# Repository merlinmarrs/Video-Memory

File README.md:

# Video-Memory

A series of PCBs to explore storing pixel information for VGA display.

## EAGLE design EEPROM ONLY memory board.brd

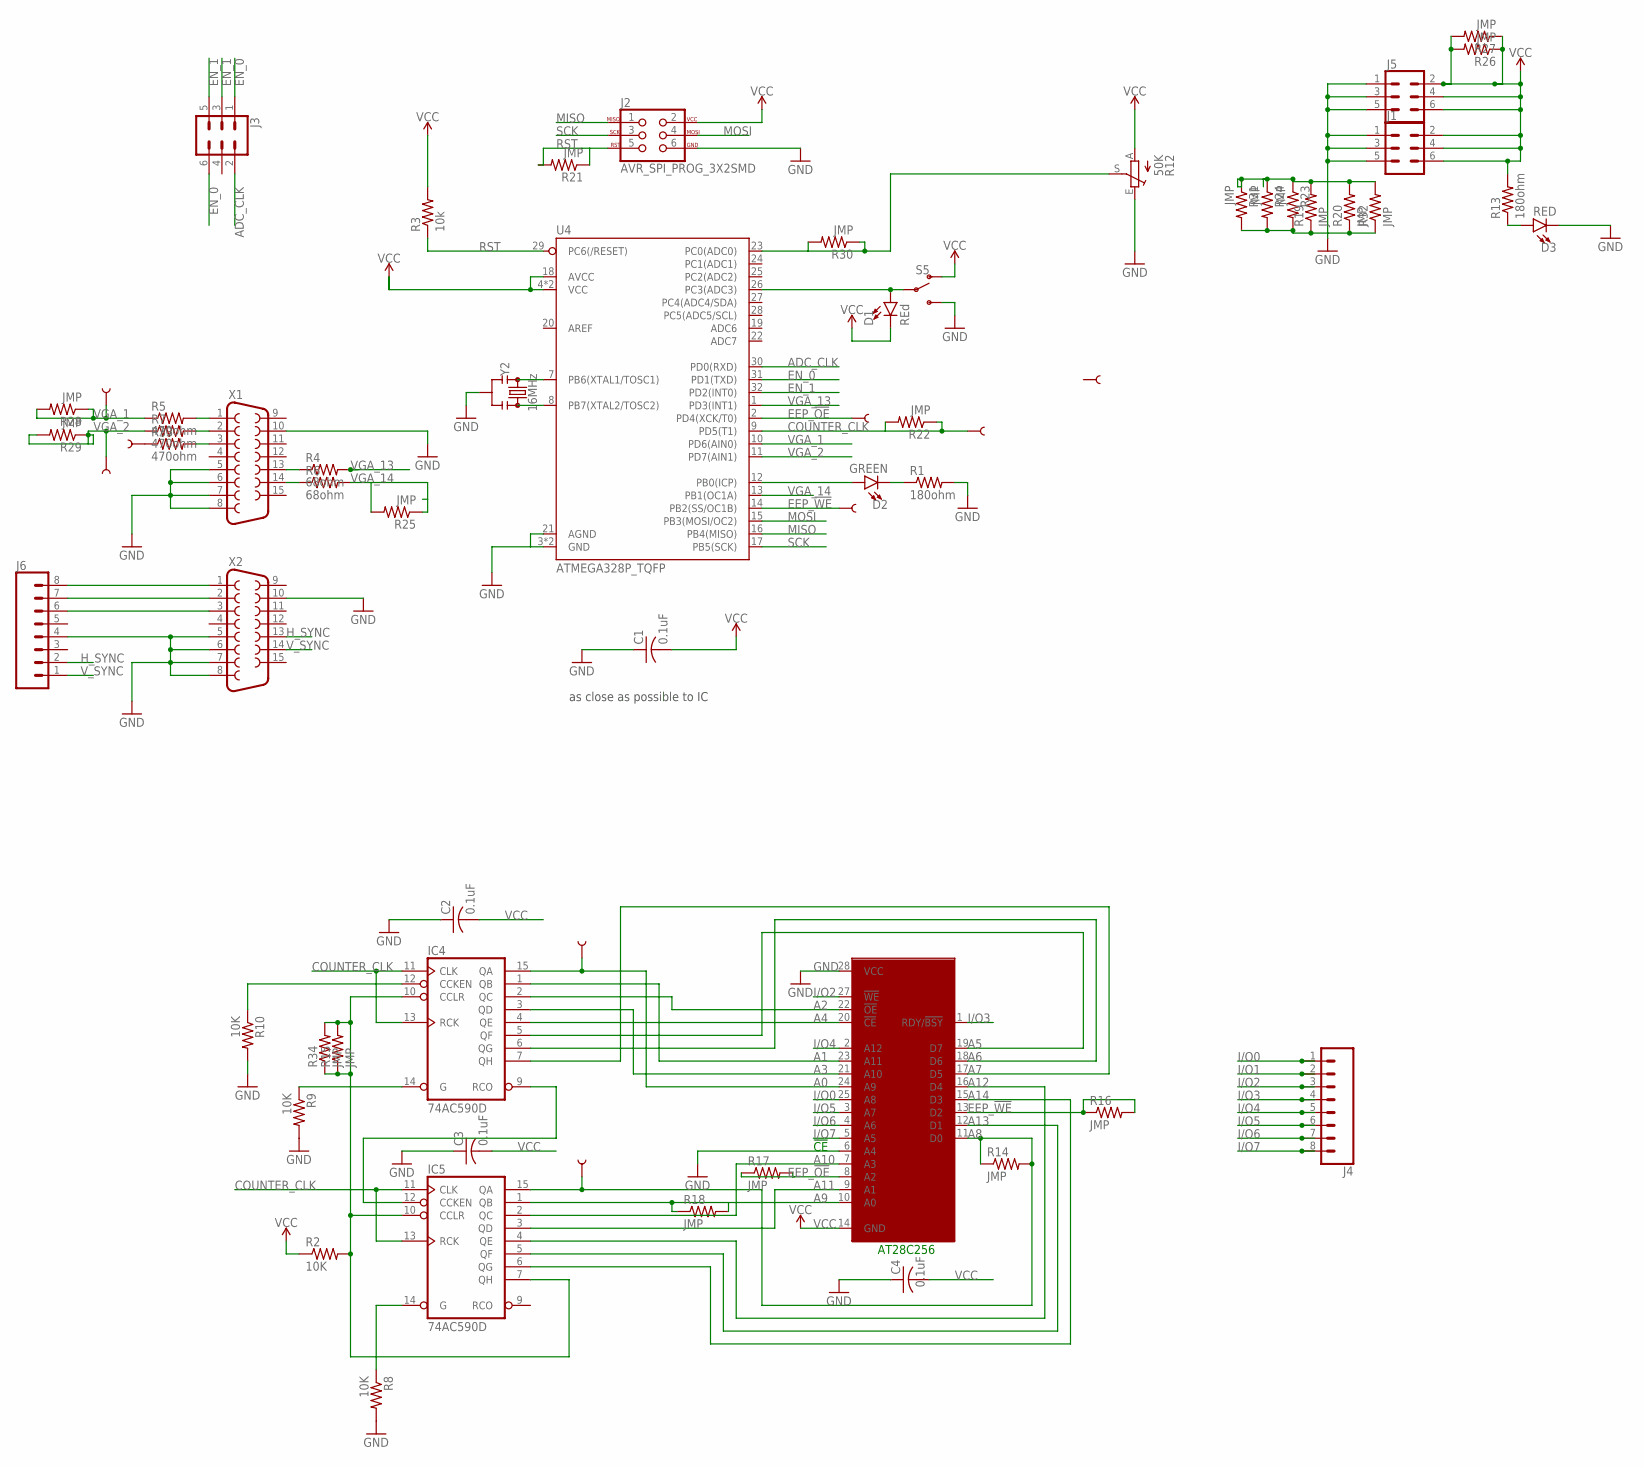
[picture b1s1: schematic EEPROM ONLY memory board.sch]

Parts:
C1, C2, C3, C4: 0.1uF; C1206
D1: REd; LED-1206
D2: GREEN; LED-1206
D3: RED; LED-1206
IC1: 28C64AVS; VSOP28-8X13
IC4, IC5: 74AC590D; SO16
J1, J3, J5: CONN_03X2FEMALE_SMD; 2X3_SMD
J2: AVR_SPI_PROG_3X2SMD; 2X3_SMT_POSTS
J4, J6: CONN_08SMD-STRAIGHT-ALT-FEMALE; 1X08_SMD_ALT
R1, R13: 180ohm; R1206
R2, R8, R9, R10: 10K; R1206
R3: 10k; R1206
R4, R6: 68ohm; R1206
R5, R7, R33: 470ohm; R1206
R12: 50K; CA9V
R14, R15, R16, R17, R18, R19, R20, R21, R22, R23, R24, R25, R26, R27, R28, R29, R30, R31, R32, R34: JMP; R1206
RX1, RX2, RX3, RX4, RX5, RX6, RX7, RX8, RX9: TEST-POINT3; PAD.03X.03
S5: SWITCH-SPDT-SMD-AYZ0202; SWITCH_DPDT_SMD_AYZ0202
U4: ATMEGA328P_TQFP; TQFP32-08
X1, X2: F15HP
Y2: 16MHz; RESONATOR-SMD-3.2X1.3

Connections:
A0: IC1.24 (A9), IC4.15 (QA), RX5.P$1
A1: IC1.23 (A11), IC4.1 (QB)
A2: IC1.22 (!OE), IC4.2 (QC)
A3: IC1.21 (A10), IC4.3 (QD)
A4: IC1.20 (!CE), IC4.4 (QE)
A5: IC1.19 (D7), IC4.5 (QF)
A6: IC1.18 (D6), IC4.6 (QG)
A7: IC1.17 (D5), IC4.7 (QH)
A8: IC1.11 (D0), IC5.15 (QA), R14.1, R14.2, RX6.P$1
A9: IC1.10 (A0), IC5.1 (QB), R18.1, R18.2
A10: IC1.7 (A3), IC5.2 (QC)
A11: IC1.9 (A1), IC5.3 (QD)
A12: IC1.16 (D4), IC5.4 (QE)
A13: IC1.12 (D1), IC5.5 (QF)
A14: IC1.15 (D3), IC5.6 (QG)
ADC_CLK: J3.2, U4.30 (PD0(RXD))
COUNTER_CLK: IC4.11 (CLK), IC4.13 (RCK), IC5.11 (CLK), IC5.13 (RCK), R22.1, R22.2, RX3.P$1, U4.9 (PD5(T1))
EEP_!OE: IC1.8 (A2), R17.1, R17.2, RX2.P$1, U4.2 (PD4(XCK/T0))
EEP_!WE: IC1.13 (D2), R16.1, R16.2, RX4.P$1, U4.14 (PB2(SS/OC1B))
EN_0: J3.1, J3.6, U4.31 (PD1(TXD))
EN_1: J3.3, J3.5, U4.32 (PD2(INT0))
GND: C1.1, C2.1, C3.1, C4.1, D3.C, IC1.6 (A4), IC1.28 (VCC), IC4.8 (GND), IC5.8 (GND), J1.1, J1.3, J1.5, J2.6, J5.1, J5.3, J5.5, J6.4, R1.2, R8.2, R9.2, R10.2, R12.E, R19.1, R19.2, R20.1, R20.2, R23.1, R23.2, R24.1, R24.2, R31.1, R31.2, R32.1, R32.2, S5.3 (S), U4.3 (GND), U4.5 (GND), U4.21 (AGND), X1.5, X1.6, X1.7, X1.8, X1.10, X2.5, X2.6, X2.7, X2.8, X2.10, Y2.2
H_SYNC: J6.2, X2.13
I/O0: IC1.25 (A8), J4.1
I/O1: J4.2
I/O2: IC1.27 (!WE), J4.3
I/O3: IC1.1 (RDY/!BSY), J4.4
I/O4: IC1.2 (A12), J4.5
I/O5: IC1.3 (A7), J4.6
I/O6: IC1.4 (A6), J4.7
I/O7: IC1.5 (A5), J4.8
MISO: J2.1, U4.16 (PB4(MISO))
MOSI: J2.4, U4.15 (PB3(MOSI/OC2))
unnamed: R5.2, X1.1
unnamed: R7.2, X1.2
unnamed: D3.A, R13.1
unnamed: R4.1, X1.13
unnamed: R6.1, X1.14
unnamed: IC4.9 (RCO), IC5.12 (CCKEN)
unnamed: U4.7 (PB6(XTAL1/TOSC1)), Y2.1
unnamed: U4.8 (PB7(XTAL2/TOSC2)), Y2.3
unnamed: IC5.14 (G), R8.1
unnamed: IC4.14 (G), R9.1
unnamed: IC4.12 (CCKEN), R10.1
unnamed: IC4.10 (CCLR), IC5.7 (QH), IC5.10 (CCLR), R2.2, R15.1, R15.2, R34.1, R34.2
unnamed: D1.A, S5.2, U4.26 (PC3(ADC3))
unnamed: J6.8, X2.1
unnamed: J6.7, X2.2
unnamed: D2.A, U4.12 (PB0(ICP))
unnamed: R33.2, X1.3
unnamed: D2.C, R1.1
unnamed: R33.1, RX7.P$1
unnamed: J6.6, X2.3
unnamed: R12.S, R30.1, R30.2, U4.23 (PC0(ADC0))
RST: J2.5, R3.1, R21.1, R21.2, U4.29 (PC6(/RESET))
SCK: J2.3, U4.17 (PB5(SCK))
VCC: C1.2, C2.2, C3.2, C4.2, D1.C, IC1.14 (GND), IC4.16 (VCC), IC5.16 (VCC), J1.2, J1.4, J1.6, J2.2, J5.2, J5.4, J5.6, R2.1, R3.2, R12.A, R13.2, R26.1, R26.2, R27.1, R27.2, S5.1 (O), U4.4 (VCC), U4.6 (VCC), U4.18 (AVCC)
VGA_1: R5.1, R28.1, R28.2, RX8.P$1, U4.10 (PD6(AIN0))
VGA_2: R7.1, R29.1, R29.2, RX9.P$1, U4.11 (PD7(AIN1))
VGA_13: R4.2, U4.1 (PD3(INT1))
VGA_14: R6.2, R25.1, R25.2, U4.13 (PB1(OC1A))
V_SYNC: J6.1, X2.14

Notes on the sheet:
as close as possible to IC
AT28C256
!CE

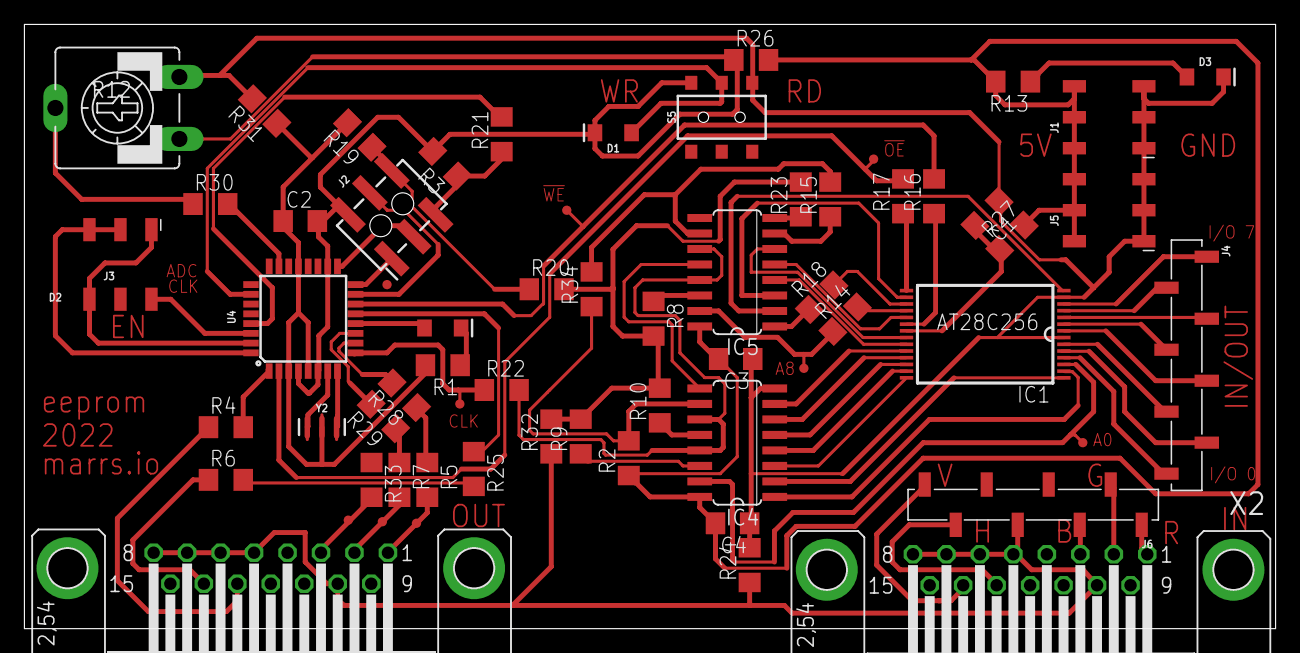
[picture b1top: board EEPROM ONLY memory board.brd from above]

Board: 2 copper layers, 102.5 x 49.5 mm, 63 parts (0 on the bottom side), 61 nets.

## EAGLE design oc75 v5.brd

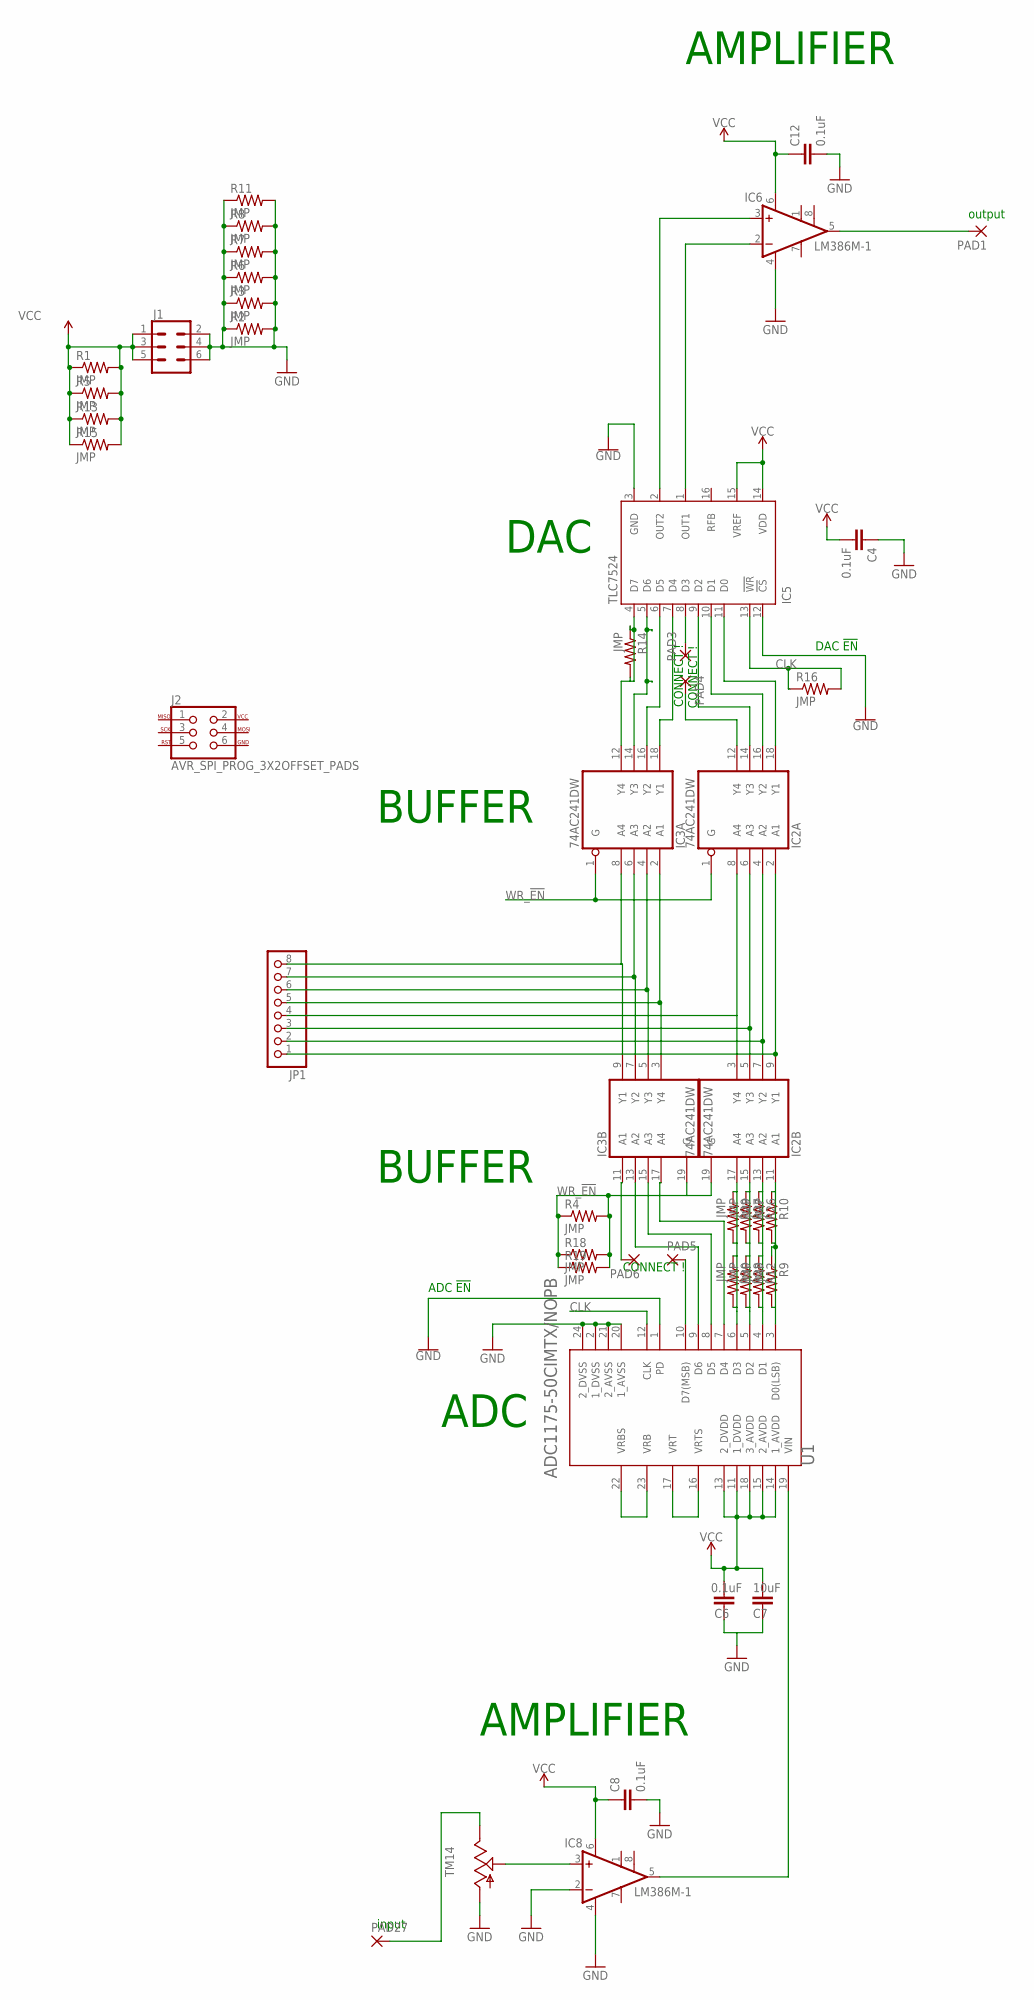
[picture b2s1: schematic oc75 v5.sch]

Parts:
C4, C6, C8, C12: 0.1uF; 1206
C7: 10uF; 1206
IC2, IC3: 74AC241DW; SO20W
IC5: TLC7524; SO16
IC6, IC8: LM386M-1; SO08
J1: CONN_03X2FEMALE_SMD; 2X3_SMD
J2: AVR_SPI_PROG_3X2OFFSET_PADS; 2X3_OFFSET
JP1: PINHD-1X8BIG; 1X08-BIG
PAD1, PAD3, PAD4, PAD5, PAD6, PAD27: SMD2; SMD1,27-2,54
R1, R2, R3, R4, R5, R6, R7, R8, R9, R10, R11, R12, R13, R14, R15, R16, R18, R19, R26, R27, R28, R29, R30: JMP; M1206
TM14: TRIM; 6MM
U1: TEXAS_INSTRUMENTS_ADC1175-50CIMTX-NOPBTEXAS_INSTR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; TEXAS_INSTRUMENTS_ADC1175-50CIMTX-NOPB_0

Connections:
CLK: IC5.13 (!WR), R16.1, R16.2, U1.12 (CLK)
GND: C4.1, C6.1, C7.1, C8.2, C12.2, IC2.10 (GND), IC3.10 (GND), IC5.3 (GND), IC5.12 (!CS), IC6.4 (GND), IC8.2 (-IN), IC8.4 (GND), J1.2, J1.4, J1.6, R2.1, R2.2, R3.1, R3.2, R6.1, R6.2, R7.1, R7.2, R8.1, R8.2, R11.1, R11.2, TM14.A, U1.1 (PD), U1.2 (1_DVSS), U1.20 (1_AVSS), U1.21 (2_AVSS), U1.24 (2_DVSS)
unnamed: IC2.2 (A1), IC2.9 (Y1), JP1.1
unnamed: IC2.4 (A2), IC2.7 (Y2), JP1.2
unnamed: IC2.5 (Y3), IC2.6 (A3), JP1.3
unnamed: IC2.3 (Y4), IC2.8 (A4), JP1.4
unnamed: IC3.2 (A1), IC3.3 (Y4), JP1.5
unnamed: IC3.4 (A2), IC3.5 (Y3), JP1.6
unnamed: IC3.6 (A3), IC3.7 (Y2), JP1.7
unnamed: IC3.8 (A4), IC3.9 (Y1), JP1.8
unnamed: IC2.18 (Y1), IC5.11 (D0)
unnamed: IC2.16 (Y2), IC5.10 (D1)
unnamed: IC2.14 (Y3), IC5.9 (D2)
unnamed: IC2.12 (Y4), PAD4.1
unnamed: IC3.18 (Y1), IC5.7 (D4)
unnamed: IC3.16 (Y2), IC5.6 (D5)
unnamed: IC3.14 (Y3), IC5.5 (D6)
unnamed: IC3.12 (Y4), IC5.4 (D7), R14.1, R14.2
unnamed: IC2.11 (A1), R9.1, R9.2, R10.1, R10.2, U1.3 (D0(LSB))
unnamed: IC2.13 (A2), R12.1, R12.2, R26.1, R26.2, U1.4 (D1)
unnamed: IC2.15 (A3), R27.1, R27.2, R28.1, R28.2, U1.5 (D2)
unnamed: IC2.17 (A4), R29.1, R29.2, R30.1, R30.2, U1.6 (D3)
unnamed: IC3.17 (A4), U1.7 (D4)
unnamed: IC3.15 (A3), U1.8 (D5)
unnamed: IC3.13 (A2), U1.9 (D6)
unnamed: IC3.11 (A1), PAD6.1
unnamed: IC5.8 (D3), PAD3.1
unnamed: IC5.2 (OUT2), IC6.3 (+IN)
unnamed: IC5.1 (OUT1), IC6.2 (-IN)
unnamed: U1.16 (VRTS), U1.17 (VRT)
unnamed: U1.22 (VRBS), U1.23 (VRB)
unnamed: IC6.5 (OUT), PAD1.1
unnamed: PAD5.1, U1.10 (D7(MSB))
unnamed: PAD27.1, TM14.E
unnamed: IC8.3 (+IN), TM14.S
unnamed: IC8.5 (OUT), U1.19 (VIN)
VCC: C4.2, C6.2, C7.2, C8.1, C12.1, IC2.20 (VCC), IC3.20 (VCC), IC5.14 (VDD), IC5.15 (VREF), IC6.6 (VS), IC8.6 (VS), J1.1, J1.3, J1.5, R1.1, R1.2, R5.1, R5.2, R13.1, R13.2, R15.1, R15.2, U1.11 (1_DVDD), U1.13 (2_DVDD), U1.14 (1_AVDD), U1.15 (2_AVDD), U1.18 (3_AVDD)
WR_!EN: IC2.1 (G), IC2.19 (G), IC3.1 (G), IC3.19 (G), R4.1, R4.2, R18.1, R18.2, R19.1, R19.2

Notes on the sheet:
BUFFER
DAC
ADC
AMPLIFIER
input
ADC !EN
DAC !EN
output
CONNECT !

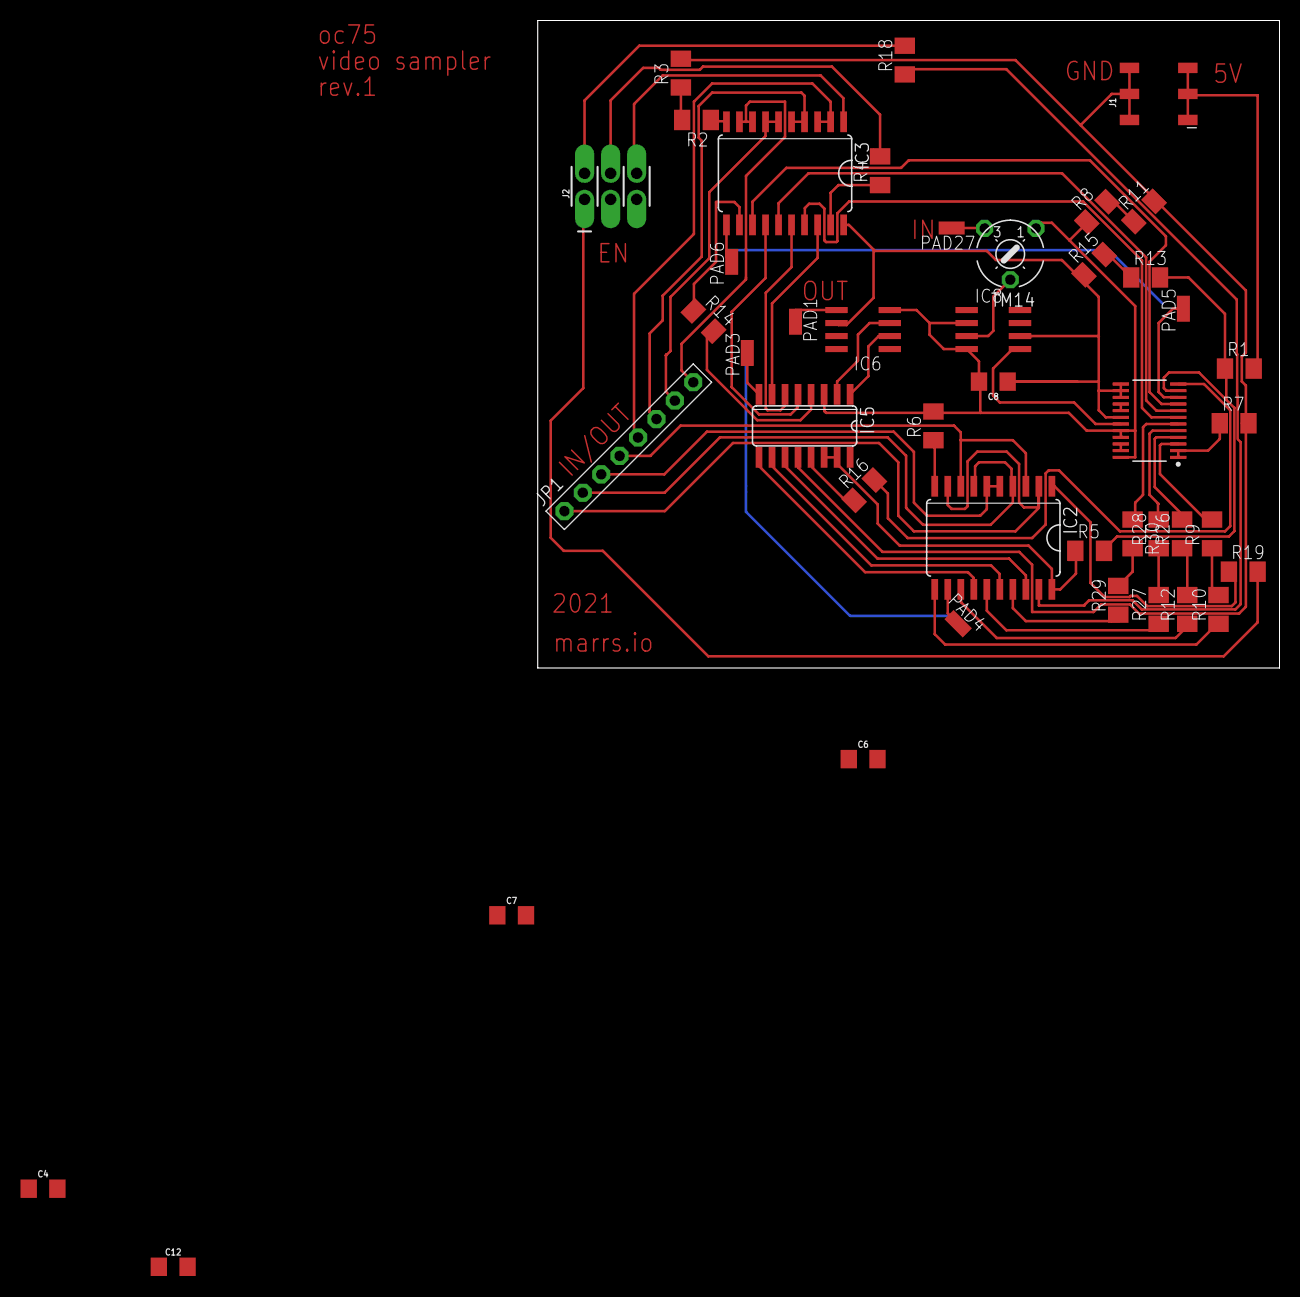
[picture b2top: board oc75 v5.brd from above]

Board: 2 copper layers, 72.4 x 63.2 mm, 44 parts (0 on the bottom side), 38 nets.

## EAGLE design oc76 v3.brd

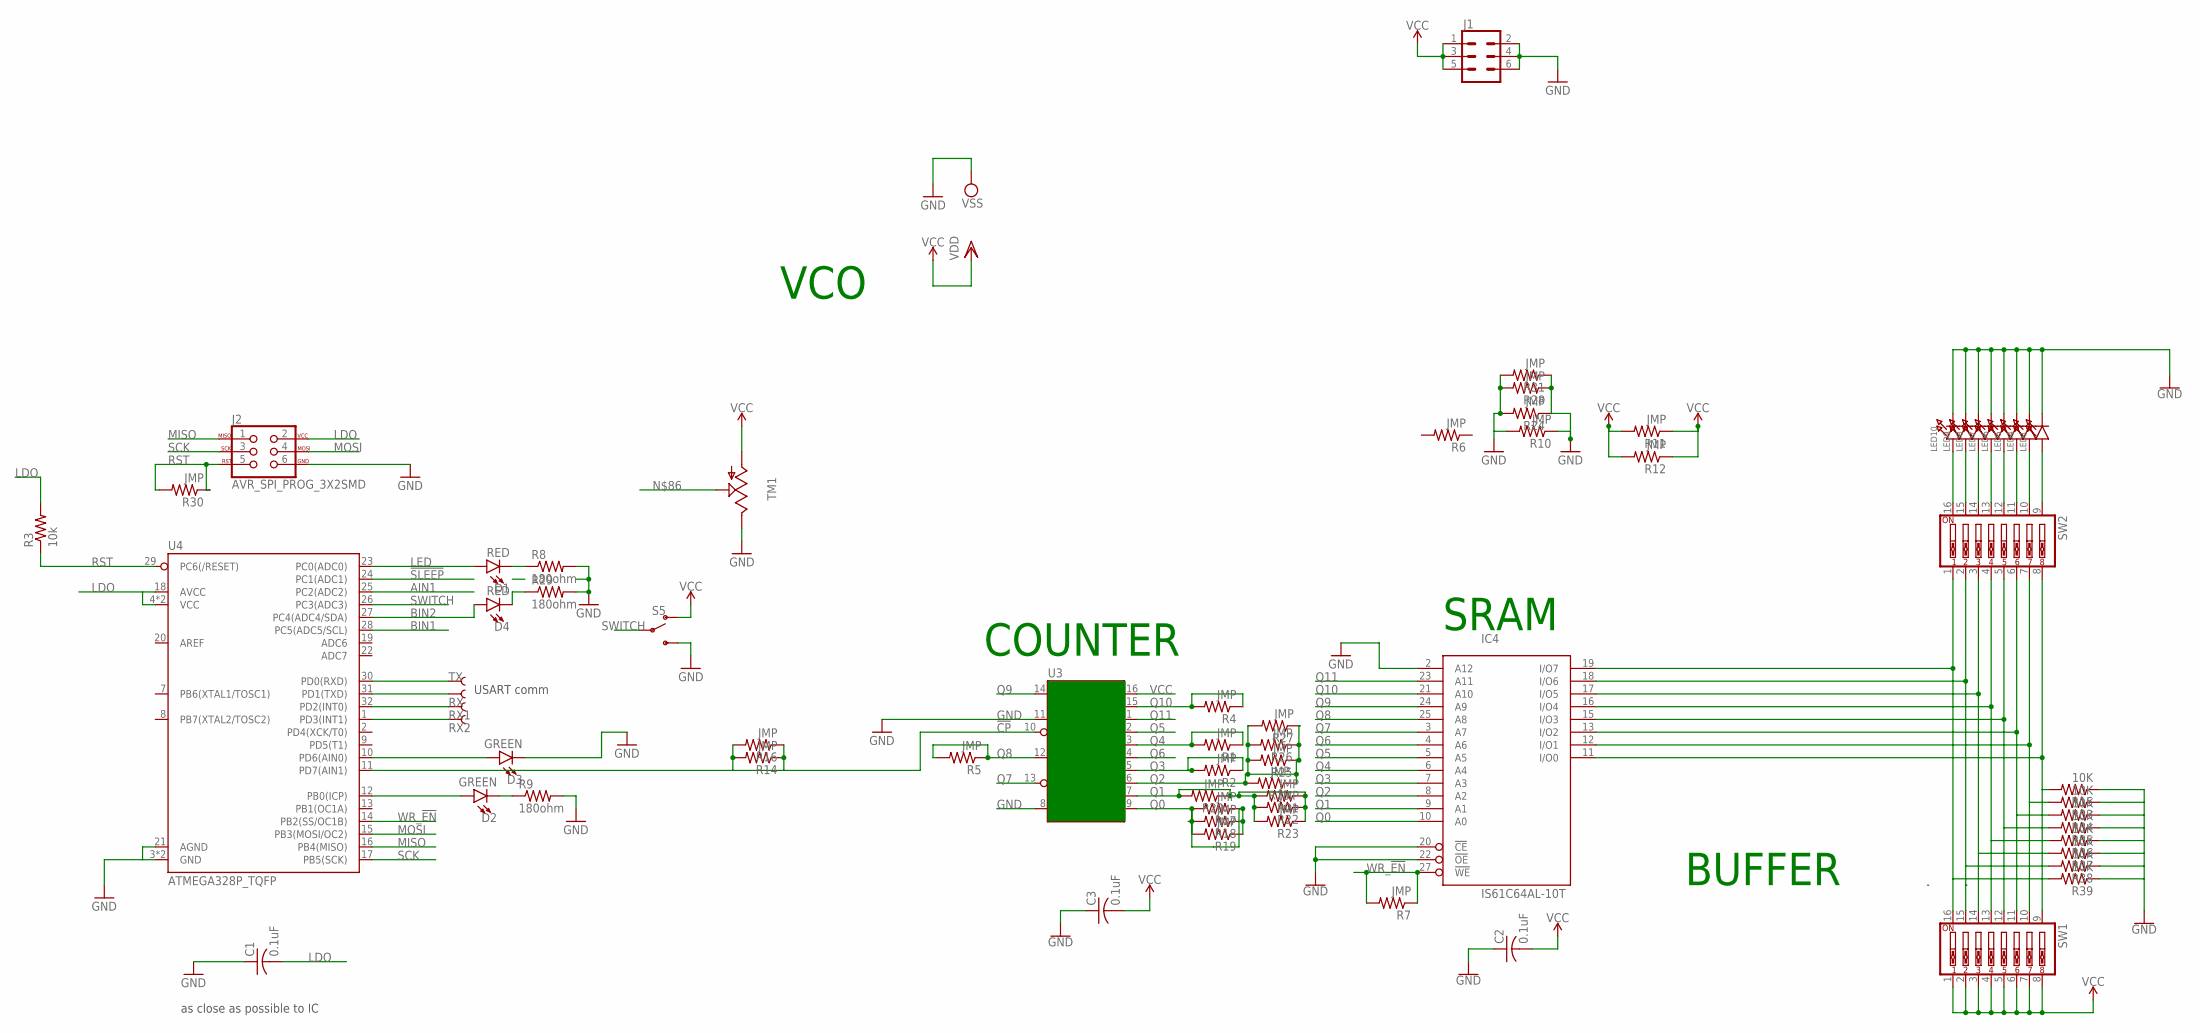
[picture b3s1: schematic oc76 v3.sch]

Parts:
C1, C2, C3: 0.1uF; C1206
D1, D4: RED; LED-1206
D2, D3: GREEN; LED-1206
IC4: IS61C64AL-10T; TSOP-I-28
J1: CONN_03X2FEMALE_SMD; 2X3_SMD
J2: AVR_SPI_PROG_3X2SMD; 2X3_SMT_POSTS
LED1, LED4, LED5, LED6, LED7, LED8, LED9, LED10: LED1206; CHIPLED_1206
R1, R2, R4, R5, R6, R7, R10, R11, R12, R13, R14, R16, R17, R18, R19, R20, R21, R22, R23, R24, R25, R26, R27, R28, R30, R31: JMP; M1206
R3: 10k; R1206
R8, R9, R29: 180ohm; R1206
R15, R33, R34, R35, R36, R37, R38, R39: 10K; M1206
RX, RX1, RX2: TEST-POINT3; PAD.03X.03
S5: SWITCH-SPDT-SMD-AYZ0202; SWITCH_DPDT_SMD_AYZ0202
SW1, SW2: DIP-08-SMT-HALFSIZE; DIPSWITCH-08-50MIL
TM1: TRIM; 6MM
TX: TEST-POINT3; PAD.03X.03
U3: 74595; TSSOP16
U4: ATMEGA328P_TQFP; TQFP32-08

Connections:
!CP: R14.1, R14.2, R16.1, R16.2, U3.10 (SCL), U4.11 (PD7(AIN1))
!SLEEP: U4.24 (PC1(ADC1))
AIN1: U4.25 (PC2(ADC2))
BIN1: U4.28 (PC5(ADC5/SCL))
BIN2: D4.A, U4.27 (PC4(ADC4/SDA))
GND: C1.1, C2.1, C3.1, D3.C, IC4.2 (A12), IC4.14 (GND), IC4.20 (!CE), IC4.22 (!OE), J1.2, J1.4, J1.6, J2.6, LED1.C, LED4.C, LED5.C, LED6.C, LED7.C, LED8.C, LED9.C, LED10.C, R8.2, R9.2, R10.1, R10.2, R15.1, R24.1, R24.2, R28.1, R28.2, R29.2, R31.1, R31.2, R33.1, R34.1, R35.1, R36.1, R37.1, R38.1, R39.1, S5.3 (S), TM1.E, U3.8 (GND), U3.11 (SCK), U4.3 (GND), U4.5 (GND), U4.21 (AGND)
LDO: C1.2, J2.2, R3.2, U4.4 (VCC), U4.6 (VCC), U4.18 (AVCC)
LED: D1.A, U4.23 (PC0(ADC0))
MISO: J2.1, U4.16 (PB4(MISO))
MOSI: J2.4, U4.15 (PB3(MOSI/OC2))
unnamed: D4.C, R29.1
unnamed: RX1.P$1, U4.32 (PD2(INT0))
unnamed: RX2.P$1, U4.1 (PD3(INT1))
unnamed: D3.A, U4.10 (PD6(AIN0))
unnamed: TX.P$1, U4.30 (PD0(RXD))
unnamed: RX.P$1, U4.31 (PD1(TXD))
unnamed: D2.A, U4.12 (PB0(ICP))
unnamed: D1.C, R8.1
unnamed: D2.C, R9.1
unnamed: IC4.19 (I/O7), R39.2, SW1.16, SW2.1
unnamed: IC4.16 (I/O4), R36.2, SW1.13, SW2.4
unnamed: IC4.18 (I/O6), R38.2, SW1.15, SW2.2
unnamed: IC4.17 (I/O5), R37.2, SW1.14, SW2.3
unnamed: IC4.15 (I/O3), R35.2, SW1.12, SW2.5
unnamed: IC4.13 (I/O2), R34.2, SW1.11, SW2.6
unnamed: IC4.12 (I/O1), R33.2, SW1.10, SW2.7
unnamed: IC4.11 (I/O0), R15.2, SW1.9, SW2.8
unnamed: LED4.A, SW2.10
unnamed: LED5.A, SW2.11
unnamed: LED10.A, SW2.16
unnamed: LED9.A, SW2.15
unnamed: LED8.A, SW2.14
unnamed: LED7.A, SW2.13
unnamed: LED6.A, SW2.12
unnamed: LED1.A, SW2.9
Q0: IC4.10 (A0), R17.1, R17.2, R18.1, R18.2, R19.1, R19.2, U3.9 (QH*)
Q1: IC4.9 (A1), R20.1, R20.2, R21.1, R21.2, R22.1, R22.2, R23.1, R23.2, U3.7 (QH)
Q2: IC4.8 (A2), R13.1, R13.2, R25.1, R25.2, R26.1, R26.2, R27.1, R27.2, U3.6 (QG)
Q3: IC4.7 (A3), R2.1, R2.2, U3.5 (QF)
Q4: IC4.6 (A4), R1.1, R1.2, U3.3 (QD)
Q5: IC4.5 (A5), U3.2 (QC)
Q6: IC4.4 (A6), U3.4 (QE)
Q7: IC4.3 (A7), U3.13 (G)
Q8: IC4.25 (A8), R5.1, R5.2, U3.12 (RCK)
Q9: IC4.24 (A9), U3.14 (SER)
Q10: IC4.21 (A10), R4.1, R4.2, U3.15 (QA)
Q11: IC4.23 (A11), U3.1 (QB)
RST: J2.5, R3.1, R30.1, R30.2, U4.29 (PC6(/RESET))
SCK: J2.3, U4.17 (PB5(SCK))
SWITCH: S5.2, U4.26 (PC3(ADC3))
VCC: C2.2, C3.2, J1.1, J1.3, J1.5, R11.1, R11.2, R12.1, R12.2, S5.1 (O), SW1.1, SW1.2, SW1.3, SW1.4, SW1.5, SW1.6, SW1.7, SW1.8, TM1.A, U3.16 (VCC)
VDD: IC4.28 (VDD)
WR_!EN: IC4.27 (!WE), R7.1, R7.2, U4.14 (PB2(SS/OC1B))

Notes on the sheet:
VCO
COUNTER
SRAM
BUFFER
USART comm
as close as possible to IC

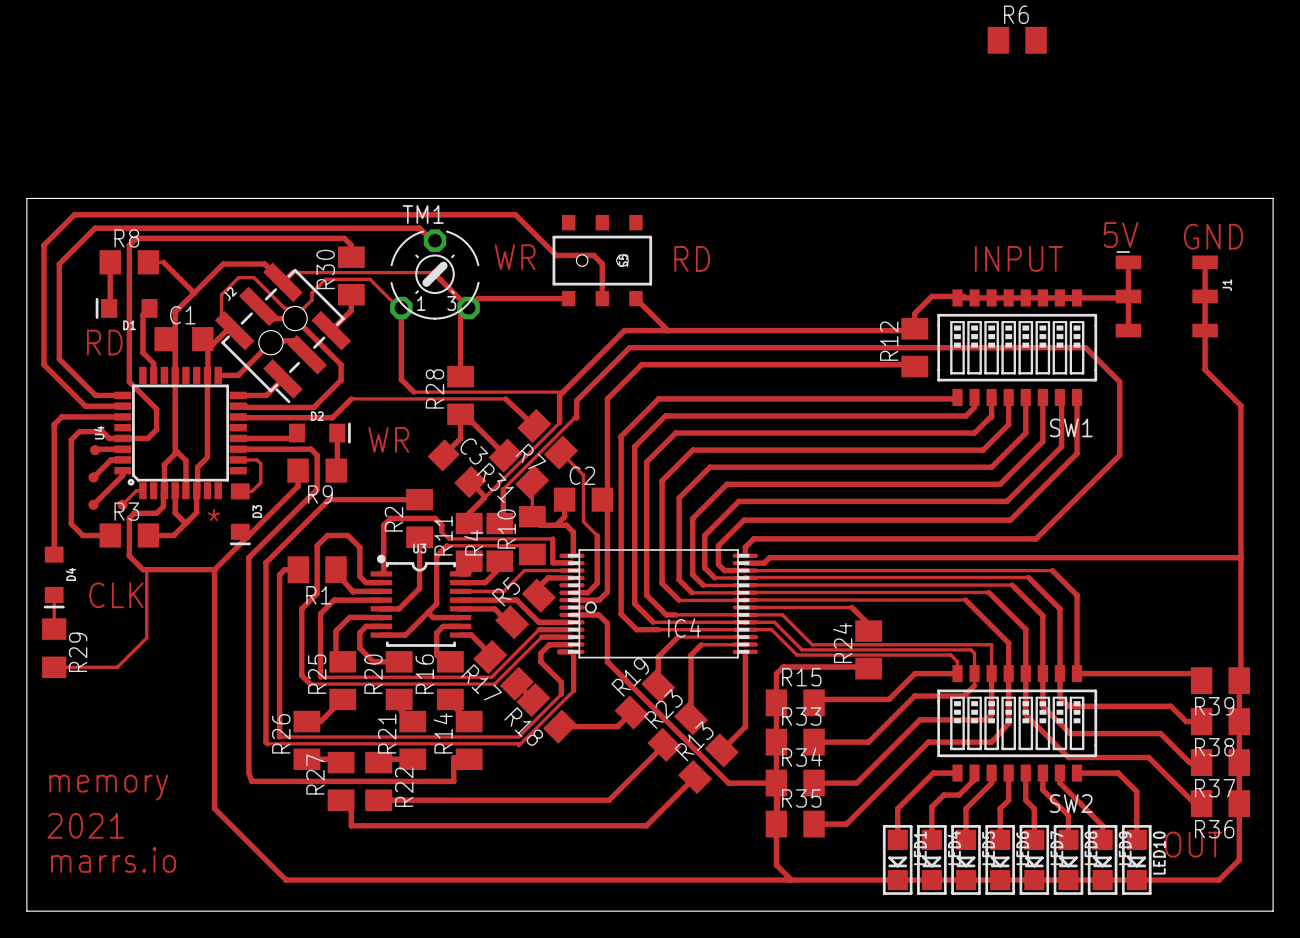
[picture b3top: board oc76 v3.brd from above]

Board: 2 copper layers, 92.7 x 53.0 mm, 66 parts (0 on the bottom side), 49 nets.

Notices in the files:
parts and their libraries:
SparkFun-IC-Microcontroller: Licensing: Creative Commons ShareAlike 4.0 International - https://creativecommons.org/licenses/by-sa/4.0
tlc7524: Copyright (C) 2009, Vitaly Perov (vit346@gmail.com)
